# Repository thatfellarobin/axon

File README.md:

# Axon
[![CC BY-NC-SA 4.0][cc-by-nc-sa-shield]][cc-by-nc-sa]

*Axon version 1.0 built with Durock T1 and GMK Bento*

⚠️ **Using the live github version is not recommended. Please use [a release](https://github.com/thatfellarobin/axon/releases) instead. Performance is not guaranteed outside of official sale (which have not existed so far).**

Axon is a 40% custom mechanical keyboard with an emphasis on symmetrically placed through-hole components, inspired by other keyboards such as [gingham](https://github.com/yiancar/gingham_pcb) and [plaid](https://github.com/hsgw/plaid). Axon runs on an ATmega328P using VUSB and QMK.

Notable features include an [HHKB-style](https://happyhackingkb.com/) layout with missing lower corners, and a split spacebar. I never use my right thumb to hit spacebar, so the split allows me to use my right thumb to access additional keyboard layers. A full write-up can be found [on my website](https://www.robinliu.me/axon).

### Images

**Layout:**

**PCB EDA Screenshot:**

### Component Libraries

**Symbols:**
- [Keyboard symbols by Hasu](https://github.com/tmk/kicad_lib_tmk)

**Footprints:**
- [Keyswitches by Daprice](https://github.com/daprice/keyswitches.pretty), but modified for my own tastes/uses.
- My own footprints for silkscreen art. Can be found in `lib/`

### Versions
**1.0:**
- Initial release, production version for personal use.

**1.1:**
- Spacebar widths can be swapped (i.e. 2.25u-2.75u instead of 2.75u-2.25u).
- Added support for 7u and 6.25u spacebars.
- Art is now exposed copper instead of silkscreen.
- Added an indicator LED, which is controlled through QMK as a backlight. This is to enable hardware PWM dimming.
- Update screw placements to ensure acrylic cover symmetry along both x and y axis.
- Fixed issues with stabilizer interference.
- Optimize decoupling capacitor placement.
- Polyfuse now has room to lay horizontally if desired.
- Back side silkscreen accurately reflects default layout.
- Connected shield to ground.
- Numerous minor layout and routing changes.
- Added version number to rear silkscreen.
- Updated license.

## License
This work is licensed under a
[Creative Commons Attribution-NonCommercial-ShareAlike 4.0 International License][cc-by-nc-sa].

[![CC BY-NC-SA 4.0][cc-by-nc-sa-image]][cc-by-nc-sa]

[cc-by-nc-sa]: http://creativecommons.org/licenses/by-nc-sa/4.0/
[cc-by-nc-sa-image]: https://licensebuttons.net/l/by-nc-sa/4.0/88x31.png
[cc-by-nc-sa-shield]: https://img.shields.io/badge/License-CC%20BY--NC--SA%204.0-lightgrey.svg

If you have built upon this project and have significantly altered the design, the non-commercial clause can be waived with explicit permission.

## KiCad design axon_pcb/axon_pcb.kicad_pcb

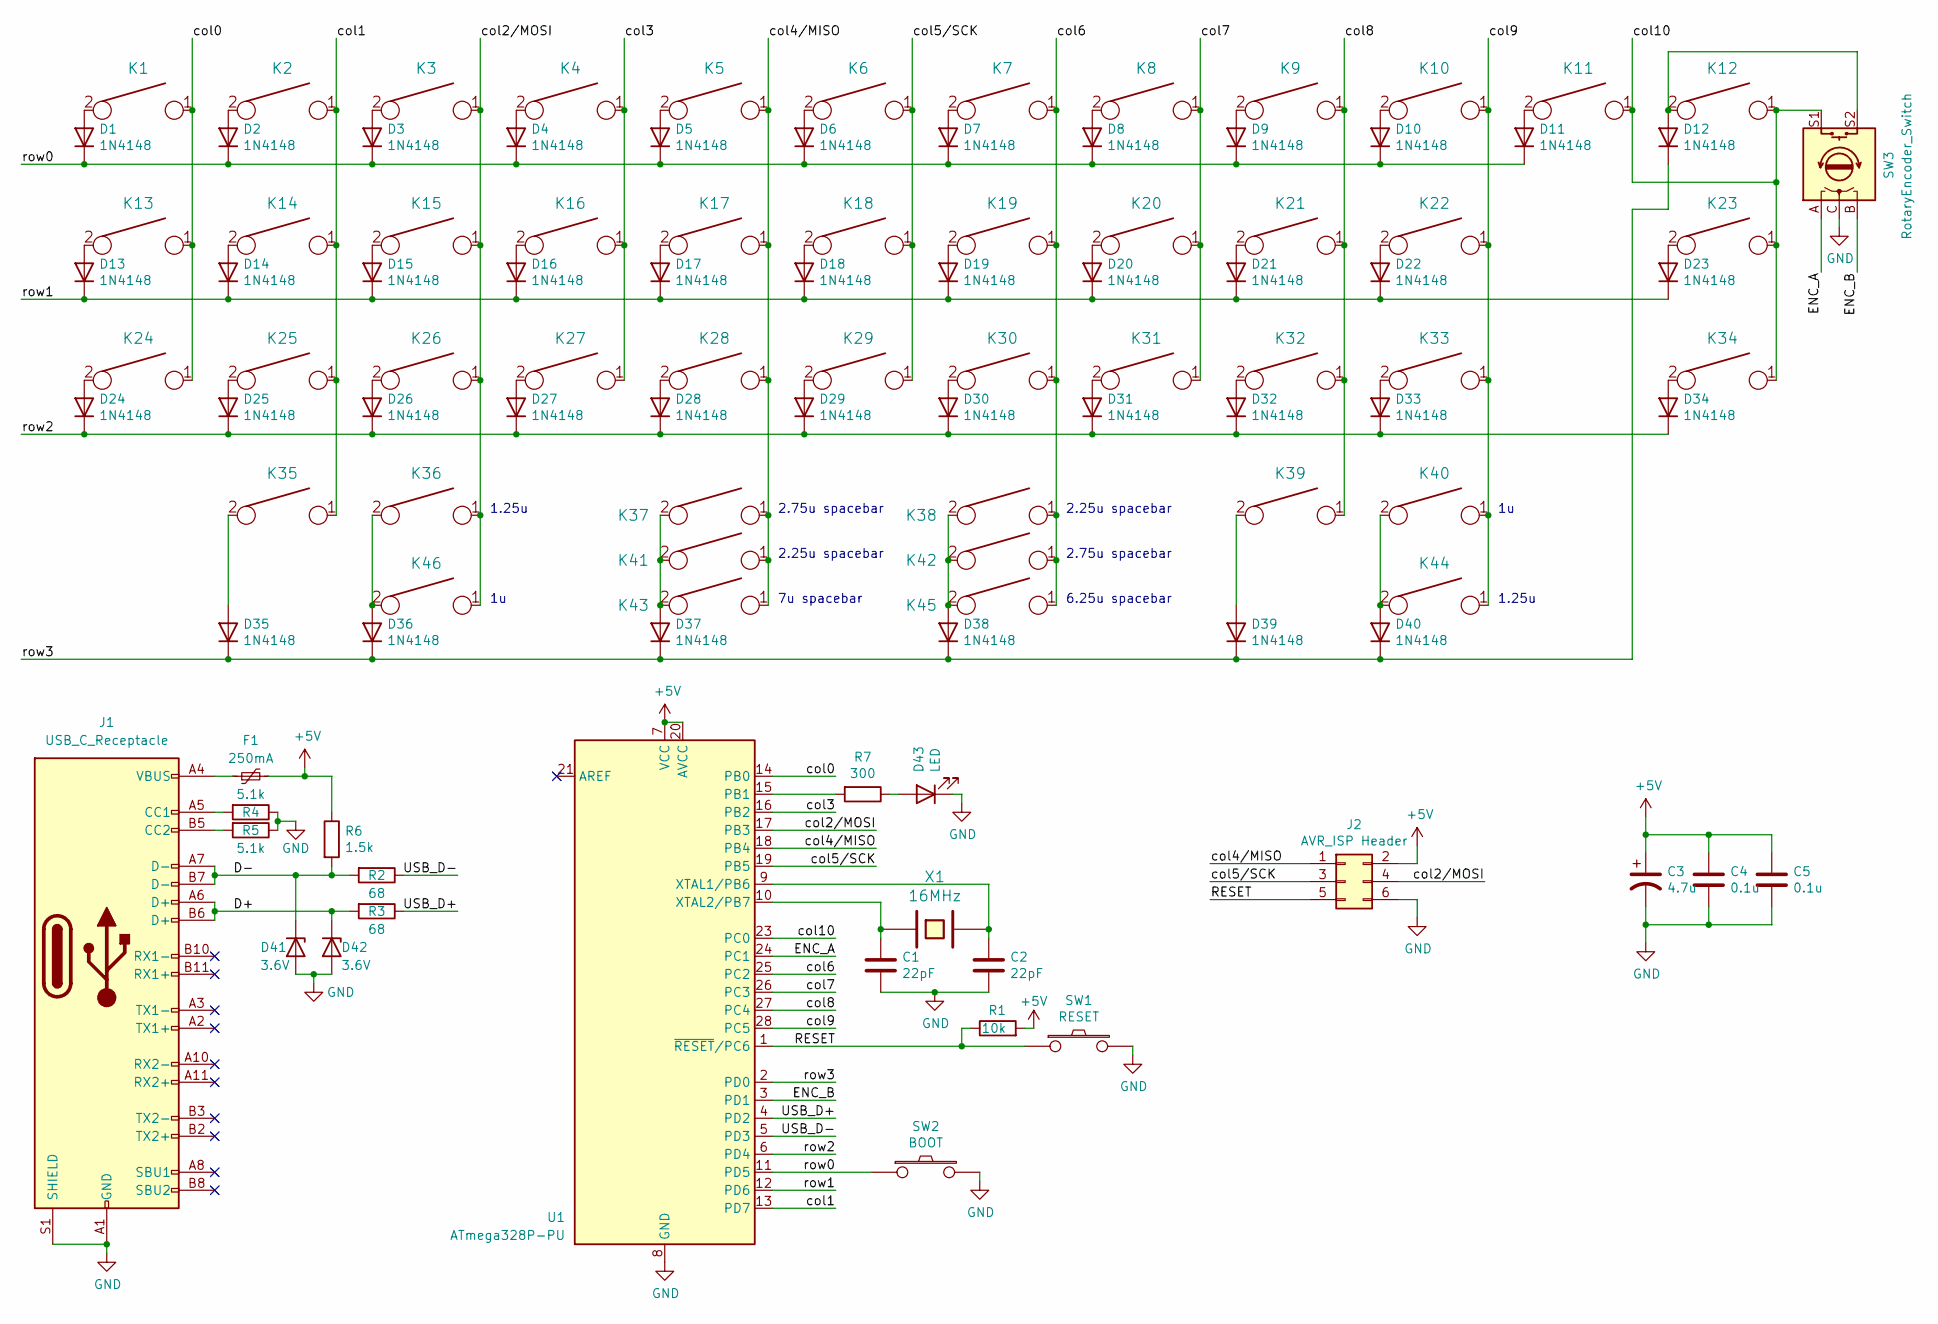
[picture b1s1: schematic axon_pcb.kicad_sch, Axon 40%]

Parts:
C1, C2: 22pF; C_Disc_D3.0mm_W1.6mm_P2.50mm
C3: 4.7u; CP_Radial_D4.0mm_P1.50mm
C4, C5: 0.1u; C_Disc_D4.3mm_W1.9mm_P5.00mm
D1, D2, D3, D4, D5, D6, D7, D8, D9, D10, D11, D12, D13, D14, D15, D16, D17, D18, D19, D20, D21, D22, D23, D24, D25, D26, D27, D28, D29, D30, D31, D32, D33, D34, D35, D36, D37, D38, D39, D40: 1N4148; D_DO-35_SOD27_P7.62mm_Horizontal_personal
D41, D42: 3.6V; D_DO-35_SOD27_P7.62mm_Horizontal_personal
D43: LED; LED_D5.0mm
F1: 250mA; C_Disc_D5.0mm_W2.5mm_P5.00mm
J1: USB_C_Receptacle; USB_C_Receptacle_GCT_USB4085_personalized
J2: AVR_ISP Header; PinHeader_2x03_P2.54mm_Vertical
K1, K2, K3, K4, K5, K6, K7, K8, K9, K10, K11, K12, K13, K14, K15, K16, K17, K18, K19, K20, K21, K22, K23, K24, K25, K26, K27, K28, K29, K30, K31, K32, K33, K34: KEYSW; SW_MX_InsideSilkRef
K35, K36, K37, K38, K39, K40, K41, K42, K43, K44, K45, K46: KEYSW; SW_MX_Minimal_InsideSilkRef
R1: 10k; R_Axial_DIN0204_L3.6mm_D1.6mm_P5.08mm_Horizontal
R2, R3: 68; R_Axial_DIN0204_L3.6mm_D1.6mm_P5.08mm_Horizontal
R4, R5: 5.1k; R_Axial_DIN0204_L3.6mm_D1.6mm_P5.08mm_Horizontal
R6: 1.5k; R_Axial_DIN0204_L3.6mm_D1.6mm_P5.08mm_Horizontal
R7: 300; R_Axial_DIN0204_L3.6mm_D1.6mm_P5.08mm_Horizontal
SW1: RESET; SW_PUSH_6mm
SW2: BOOT; SW_PUSH_6mm
SW3: RotaryEncoder_Switch; RotaryEncoder_Alps_EC11E-Switch_Vertical_H20mm
U1: ATmega328P-PU; DIP-28_W7.62mm
X1: 16MHz; Crystal_HC49-4H_Vertical

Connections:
+5V: C3.1, C4.1, C5.1, F1.2, J2.2, R1.2, R6.1, U1.7 (VCC), U1.20 (AVCC)
/D+: D42.1 (K), J1.A6 (D+), J1.B6 (D+), R3.2
/D-: D41.1 (K), J1.A7 (D-), J1.B7 (D-), R2.2, R6.2
/ENC_A: SW3.A, U1.24 (PC1)
/ENC_B: SW3.B, U1.3 (PD1)
/RESET: J2.5, R1.1, SW1.1, U1.1 (~RESET/PC6)
/USB_D+: R3.1, U1.4 (PD2)
/USB_D-: R2.1, U1.5 (PD3)
/col0: K1.1, K13.1, K24.1, U1.14 (PB0)
/col1: K2.1, K14.1, K25.1, K35.1, U1.13 (PD7)
/col2/MOSI: J2.4, K3.1, K15.1, K26.1, K36.1, K46.1, U1.17 (PB3)
/col3: K4.1, K16.1, K27.1, U1.16 (PB2)
/col4/MISO: J2.1, K5.1, K17.1, K28.1, K37.1, K41.1, K43.1, U1.18 (PB4)
/col5/SCK: J2.3, K6.1, K18.1, K29.1, U1.19 (PB5)
/col6: K7.1, K19.1, K30.1, K38.1, K42.1, K45.1, U1.25 (PC2)
/col7: K8.1, K20.1, K31.1, U1.26 (PC3)
/col8: K9.1, K21.1, K32.1, K39.1, U1.27 (PC4)
/col9: K10.1, K22.1, K33.1, K40.1, K44.1, U1.28 (PC5)
/col10: K11.1, K12.1, K23.1, K34.1, SW3.S1, U1.23 (PC0)
/row0: D1.1 (K), D2.1 (K), D3.1 (K), D4.1 (K), D5.1 (K), D6.1 (K), D7.1 (K), D8.1 (K), D9.1 (K), D10.1 (K), D11.1 (K), SW2.1, U1.11 (PD5)
/row1: D13.1 (K), D14.1 (K), D15.1 (K), D16.1 (K), D17.1 (K), D18.1 (K), D19.1 (K), D20.1 (K), D21.1 (K), D22.1 (K), D23.1 (K), U1.12 (PD6)
/row2: D24.1 (K), D25.1 (K), D26.1 (K), D27.1 (K), D28.1 (K), D29.1 (K), D30.1 (K), D31.1 (K), D32.1 (K), D33.1 (K), D34.1 (K), U1.6 (PD4)
/row3: D12.1 (K), D35.1 (K), D36.1 (K), D37.1 (K), D38.1 (K), D39.1 (K), D40.1 (K), U1.2 (PD0)
GND: C1.2, C2.2, C3.2, C4.2, C5.2, D41.2 (A), D42.2 (A), D43.1 (K), J1.A1 (GND), J1.A12 (GND), J1.B1 (GND), J1.B12 (GND), J1.S1 (SHIELD), J2.6, R4.1, R5.1, SW1.2, SW2.2, SW3.C, U1.8 (GND), U1.22 (GND)
unnamed: C1.1, U1.10 (XTAL2/PB7), X1.1
unnamed: C2.1, U1.9 (XTAL1/PB6), X1.2
unnamed: D1.2 (A), K1.2
unnamed: D2.2 (A), K2.2
unnamed: D3.2 (A), K3.2
unnamed: D4.2 (A), K4.2
unnamed: D5.2 (A), K5.2
unnamed: D6.2 (A), K6.2
unnamed: D7.2 (A), K7.2
unnamed: D8.2 (A), K8.2
unnamed: D9.2 (A), K9.2
unnamed: D10.2 (A), K10.2
unnamed: D11.2 (A), K11.2
unnamed: D12.2 (A), K12.2, SW3.S2
unnamed: D13.2 (A), K13.2
unnamed: D14.2 (A), K14.2
unnamed: D15.2 (A), K15.2
unnamed: D16.2 (A), K16.2
unnamed: D17.2 (A), K17.2
unnamed: D18.2 (A), K18.2
unnamed: D19.2 (A), K19.2
unnamed: D20.2 (A), K20.2
unnamed: D21.2 (A), K21.2
unnamed: D22.2 (A), K22.2
unnamed: D23.2 (A), K23.2
unnamed: D24.2 (A), K24.2
unnamed: D25.2 (A), K25.2
unnamed: D26.2 (A), K26.2
unnamed: D27.2 (A), K27.2
unnamed: D28.2 (A), K28.2
unnamed: D29.2 (A), K29.2
unnamed: D30.2 (A), K30.2
unnamed: D31.2 (A), K31.2
unnamed: D32.2 (A), K32.2
unnamed: D33.2 (A), K33.2
unnamed: D34.2 (A), K34.2
unnamed: D35.2 (A), K35.2
unnamed: D36.2 (A), K36.2, K46.2
unnamed: D37.2 (A), K37.2, K41.2, K43.2
unnamed: D38.2 (A), K38.2, K42.2, K45.2
unnamed: D39.2 (A), K39.2
unnamed: D40.2 (A), K40.2, K44.2
unnamed: D43.2 (A), R7.1
unnamed: F1.1, J1.A4 (VBUS), J1.A9 (VBUS), J1.B4 (VBUS), J1.B9 (VBUS)
unnamed: J1.A5 (CC1), R4.2
unnamed: J1.B5 (CC2), R5.2
unnamed: R7.2, U1.15 (PB1)

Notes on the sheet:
1.25u
2.75u spacebar
6.25u spacebar
2.25u spacebar
7u spacebar

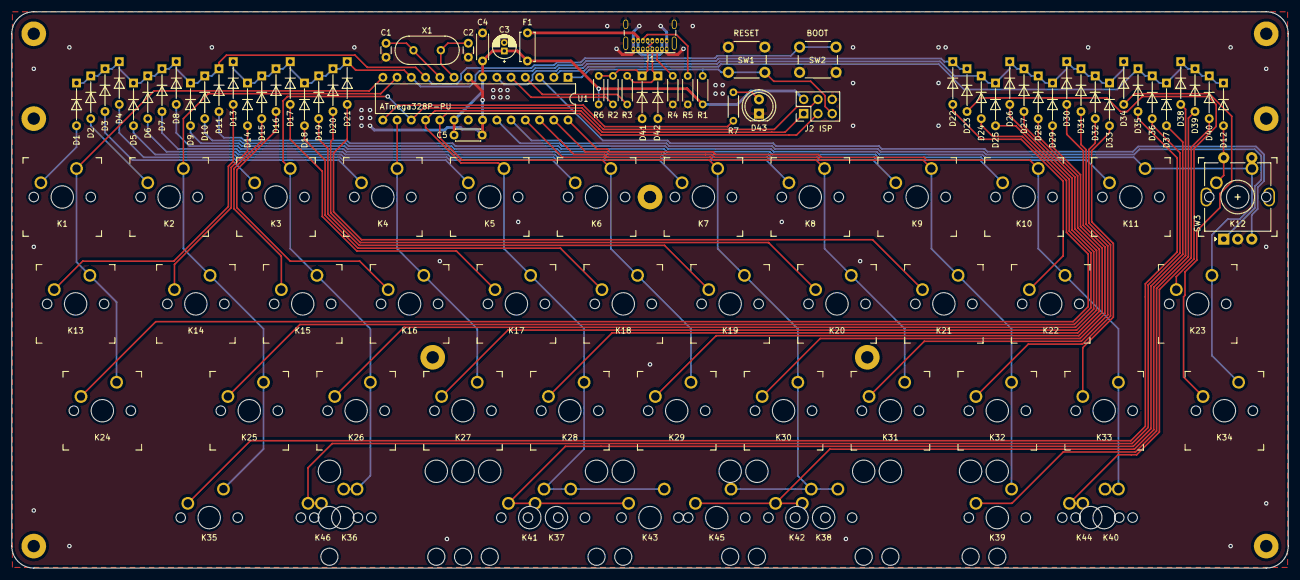
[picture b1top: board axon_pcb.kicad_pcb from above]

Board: 2 copper layers, 227.6 x 99.2 mm, 109 parts (0 on the bottom side), 71 nets.

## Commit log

2021-03-26 add readme
    very basic readme and added to .gitignore
2021-03-26 gitignore is now working
2021-03-26 fixed readme with my name
2021-03-26 added libraries used, updated readme to give credit
2021-03-30 updated header image with ISP silk
2021-03-30 tweaked component placements: - components further from edges - less difference in USB data line lengths (now less than 2 mm) - made crystal cap trace lengths more samey
2021-03-30 updated gitignore
2021-03-31 fixed libraries, final pcb version
2021-03-31 added image:
2021-03-31 tweak readme
2021-03-31 decided it's better to not redistr. other ppl's libs
2021-04-12 updated capacitor placement
2021-04-12 update readme to link hhkb
2021-04-12 added pcb photographs
2021-04-15 rerouting and added alt spacebar config
2021-04-28 additions to gitignore
2021-04-29 board updates to fix 1.0 issues
2021-04-29 update readme, change rear silk to reflect default keymap
2021-04-29 readme updates
2021-04-29 update board: acrylic fastener symmetry and elec cap placement
2021-04-30 update layout img
2021-04-30 updated bottom pcb with v2 screw holes
2021-04-30 numerous minor layout and routing tweaks
2021-05-02 central holes repositioned, rm one hole
2021-05-05 update bottom pcb
2021-05-06 adjust silkscreen
2021-05-06 update readme, remove extra files
2021-05-06 added acrylic cover dxf
2021-05-06 added 7u support
2021-05-06 adjusted footprints, added 6.25u support
2021-05-06 updated usb4085 footprint for easier handsoldering, added spacebar notes to schema
2021-05-06 add spacebar variations to layout image
2021-05-06 minor routing and position adjustments
2021-05-07 minor edits
2021-05-09 updated license
2021-05-09 typo
2021-05-10 rebase to address merge conflict
2021-05-10 minor pcb edits
2021-05-10 add dimensions to pcb editor
2021-05-11 documentation updates
2021-05-12 minor layout tweaks
    - Increased compactness of components below USB connector
    - Reduced length mismatch of USB data lines
2021-05-12 minor routing change
    - USB data line forced to pass directly through zener
2021-05-12 minor grounding improvements
2021-11-21 minor routing changes
2021-11-22 change resistor value
2021-11-22 slight position and shape changes
    - matched corner rounding to hole position
    - tweaked crystal caps position to be symmetric about crystal
    - tweaked hole positions to be more accurate
2021-11-28 add power LED
2022-03-05 update rear pcb outline
    and updated .gitignore while I was at it.
2022-03-05 gold pads
2022-03-05 change rear silk to show keyswitch numbers
    and make the schematic a little neater
2022-03-12 update license
2022-03-12 changed some silkscreen to bare copper
    - also adjusted usb connector position to be lower, sticking out from
    the board less
2022-03-21 connect shield to ground
2022-03-22 adjust diode footprint, and LED connection
    - diode footprint changed to prettier symbol
    - LED now software-controlled
2022-03-26 enable hardware pwm led dimming
2022-04-01 readme update
2022-04-02 add encoder support
2022-04-02 routing improvement
2022-04-02 routing improvements
